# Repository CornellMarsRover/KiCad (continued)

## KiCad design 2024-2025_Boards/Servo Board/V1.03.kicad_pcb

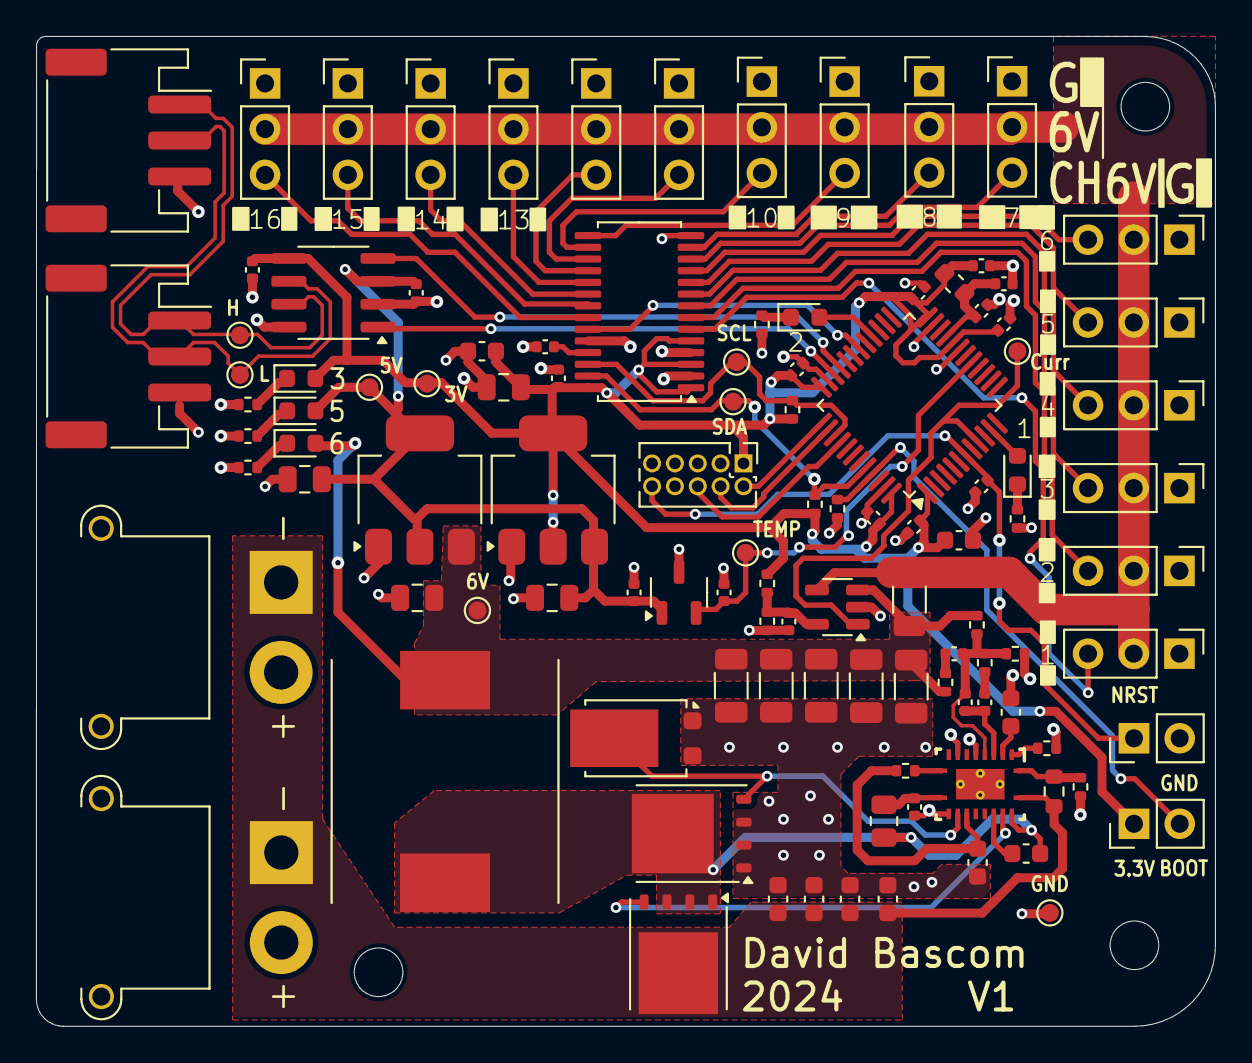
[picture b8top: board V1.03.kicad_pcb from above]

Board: 2 copper layers, 65.5 x 55.0 mm, 112 parts (0 on the bottom side), 58 nets.

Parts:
C1, C12: 10u; C_0603_1608Metric
C2, C3, C4, C5, C6, C10, C11, C13, C31: 100n; C_0402_1005Metric
C7: 10n; C_0402_1005Metric
C8, C9, C14, C15: 1u; C_0402_1005Metric
C16, C17: 0u1; C_0402_1005Metric
C27, C29: 10u; C_0805_2012Metric
C28, C30: 22u; C_0805_2012Metric
CBoot1: 0u1; C_0603_1608Metric
CC1: 2n2; C_0402_1005Metric
CC2: 47p; C_0402_1005Metric
CC3: 1.2n; C_0402_1005Metric
CIN1, CIN2, CIN3, CIN4: 4u7; C_0603_1608Metric
COUT1, COUT2, COUT3, COUT4, COUT5: 47; C_1206_3216Metric
CSS1: 47n; C_0603_1608Metric
CVcc1: 0u1; C_0603_1608Metric
Cilim1: 10p; C_0402_1005Metric
D1, D2, D3, D4, D5: GREEN; LED_0603_1608Metric
D6: SVT2060LB_R2_00001; TO-277B
FB1: 120R; L_0603_1608Metric
H1, H2, H3: MountingHole; MountingHole_2.7mm_M2.5
J1, J2: Conn_01x02_Pin; PinHeader_1x02_P2.54mm_Vertical
J3: Conn_ARM_JTAG_SWD_10; PinHeader_2x05_P1.27mm_Vertical
J4, J5: Conn_01x03_Socket; JST_PH_S3B-PH-SM4-TB_1x03-1MP_P2.00mm_Horizontal
J6, J7, J8, J9, J10, J11, J12, J13, J14, J15, J16, J17, J18, J19, J20, J21: Conn_01x03_Pin; PinHeader_1x03_P2.54mm_Vertical
J22, J23: Conn_01x02_Socket; AMASS_XT30PW-M_1x02_P2.50mm_Horizontal
L1: 2.7uH, 4.2mOhm; IND_AMDLA1306Q-101M
Q1, Q2: CSD18563Q5D; TDSON-8-1
R1, R9: 10k; R_0402_1005Metric
R2, R3: 4.7k; R_0402_1005Metric
R4: 1m; R_1206_3216Metric
R5: 100; R_0402_1005Metric
R6, R7, R16, R17: 1k; R_0402_1005Metric
R8: 2.2k; R_0402_1005Metric
RC1: 15k; R_0402_1005Metric
RC2: 3160; R_0402_1005Metric
RFB1: 20k; R_0402_1005Metric
RFB2: 3k09; R_0402_1005Metric
RPGOOD1: 20k; R_0402_1005Metric
RRT1: 20k; R_0402_1005Metric
RUV1: 20k; R_0603_1608Metric
RUV2: 3k57; R_0402_1005Metric
Rilim1: 487; R_0805_2012Metric
TP1, TP2, TP3, TP4, TP5, TP6, TP7, TP8, TP9, TP10: TestPoint; TestPoint_Pad_D1.0mm
U1: STM32G431CBT6; LQFP-48_7x7mm_P0.5mm
U2: PCA9685PW; TSSOP-28_4.4x9.7mm_P0.65mm
U3: TCAN1057AEV-Q1; SOIC-8_3.9x4.9mm_P1.27mm
U4: LM25145RGYR; RGY0020B
U5: AMS1117-3.3; SOT-223-3_TabPin2
U6: AMS1117-5.0; SOT-223-3_TabPin2
U7: INA180A4; SOT-23-5
U9: MCP9700T-E/TT; SOT-23-3

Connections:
+2.8V: C31.1, R8.2, R9.1, U7.5 (V+)
+3.3V: C1.1, C2.1, C3.1, C4.1, C5.1, C6.1, C9.1, C12.1, C13.1, C15.1, C30.1, D3.2 (A), FB1.2, J2.1, J3.1 (VTref), R2.1, R3.1, R8.1, TP9.1, U1.1 (VBAT), U1.20 (VREF+), U1.24 (VDD), U1.36 (VDD), U1.48 (VDD), U2.1 (A0), U2.3 (A2), U2.5 (A4), U2.28 (VDD), U3.5 (VIO), U5.2 (VO)
+3.3VA: C7.1, C8.1, FB1.1, U1.21 (VDDA)
+5V: C14.1, C16.1, C28.1, C29.1, D2.1 (K), D2.2 (A), R16.1, TP8.1, U3.3 (VCC), U5.3 (VI), U6.2 (VO), U9.1 (V_{DD})
+6V: C27.1, COUT1.1, COUT2.1, COUT3.1, COUT4.1, COUT5.1, D1.2 (A), J6.2, J7.2, J8.2, J9.2, J10.2, J11.2, J12.2, J13.2, J14.2, J15.2, J16.2, J17.2, J18.2, J19.2, J20.2, J21.2, L1.2, R4.1, R4.2, RC2.2, RFB1.2, TP7.1, U6.3 (VI), U7.3 (+), U7.4 (-)
+P_BATT: CIN1.1, CIN2.1, CIN3.1, CIN4.1, J22.1, J23.1, Q1.5 (D), RUV1.1, U4.20 (VIN)
/MCU/BOOT0: J2.2, R1.1, U1.45 (PB8)
/MCU/Debug_LED1: D4.2 (A), U1.11 (PA3)
/MCU/Debug_LED2: D5.2 (A), U1.28 (PB14)
/MCU/SWCLK: J3.4 (SWCLK/TCK), U1.38 (PA14)
/MCU/SWDIO: J3.2 (SWDIO/TMS), U1.37 (PA13)
/PWM Chip/EXTCLK: C11.1, U2.25 (EXTCLK)
/Power/BST: CBoot1.1, U4.17 (BST)
/Power/EN: RUV1.2, RUV2.1, U4.1 (EN_UVLO)
/Power/FB_: CC2.2, CC3.1, RC1.2, RFB1.1, RFB2.2, U4.5 (FB)
/Power/HO: Q1.4 (G), U4.18 (HO)
/Power/ILIM: Cilim1.1, Rilim1.1, U4.11 (ILIM)
/Power/LO: D6.3 (K), Q2.4 (G), U4.13 (LO)
/Power/PGOOD: RPGOOD1.2, U4.10 (PGOOD)
/Power/SS_TRK: CSS1.2, U4.3 (SS_TRK)
/Power/SW_: CBoot1.2, L1.1, Q1.1 (S), Q1.2 (S), Q1.3 (S), Q2.5 (D), Rilim1.2, U4.19 (SW)
/Power/comp: CC1.1, CC2.1, U4.4 (COMP)
/Power/rt: RRT1.2, U4.2 (RT)
CAN+: J4.1, J5.1, TP2.1, U3.7 (CANH)
CAN-: J4.2, J5.2, TP1.1, U3.6 (CANL)
CH0: J6.3, U2.6 (LED0)
CH1: J7.3, U2.7 (LED1)
CH2: J8.3, U2.8 (LED2)
CH3: J9.3, U2.9 (LED3)
CH4: J10.3, U2.10 (LED4)
CH5: J11.3, U2.11 (LED5)
CH6: J12.3, U2.12 (LED6)
CH7: J13.3, U2.13 (LED7)
CH8: J14.3, U2.15 (LED8)
CH9: J15.3, U2.16 (LED9)
CH10: J16.3, U2.17 (LED10)
CH11: J17.3, U2.18 (LED11)
CH12: J18.3, U2.19 (LED12)
CH13: J19.3, U2.20 (LED13)
CH14: J20.3, U2.21 (LED14)
CH15: J21.3, U2.22 (LED15)
CSA_OUT: TP5.1, U1.9 (PA1), U7.1
FDCAN_RX: U1.33 (PA11), U3.4 (RXD)
FDCAN_TX: U1.34 (PA12), U3.1 (TXD)
GND: C1.2, C2.2, C3.2, C4.2, C5.2, C6.2, C7.2, C8.2, C9.2, C10.2, C11.2, C12.2, C13.2, C14.2, C15.2, C16.2, C17.2, C27.2, C28.2, C29.2, C30.2, C31.2, CIN1.2, CIN2.2, CIN3.2, CIN4.2, COUT1.2, COUT2.2, COUT3.2, COUT4.2, COUT5.2, CSS1.1, CVcc1.2, Cilim1.2, D6.1 (A), D6.2 (A), J1.2, J3.3 (GND), J3.5 (GND), J3.9 (GNDDetect), J4.3, J5.3, J6.1, J7.1, J8.1, J9.1, J10.1, J11.1, J12.1, J13.1, J14.1, J15.1, J16.1, J17.1, J18.1, J19.1, J20.1, J21.1, J22.2, J23.2, Q2.1 (S), Q2.2 (S), Q2.3 (S), R1.2, R5.2, R6.2, R7.2, R9.2, R16.2, R17.2, RFB2.1, RRT1.1, RUV2.2, TP10.1, U1.19 (VSSA), U1.23 (VSS), U1.35 (VSS), U1.47 (VSS), U2.2 (A1), U2.4 (A3), U2.14 (VSS), U2.24 (A5), U3.2 (GND), U3.8 (STB), U4.6 (AGND), U4.8 (SYNCIN), U4.12 (PGND), U4.V, U5.1 (GND), U6.1 (GND), U7.2 (GND), U9.3 (GND)
NREST: C10.1, J1.1, J3.10 (~RESET), U1.7 (PG10)
unnamed: CC1.2, RC1.1
unnamed: CC3.2, RC2.1
unnamed: D1.1 (K), R5.1
unnamed: D3.1 (K), R17.1
unnamed: D4.1 (K), R6.1
unnamed: D5.1 (K), R7.1
unnamed: CVcc1.1, RPGOOD1.1, U4.14 (VCC)
PWM_OE: U1.30 (PA8), U2.23 (~OE)
PWM_SCL: R3.2, TP3.1, U1.39 (PA15), U2.26 (SCL)
PWM_SDA: R2.2, TP4.1, U1.44 (PB7), U2.27 (SDA)
SWO: J3.6 (SWO/TDO), U1.40 (PB3)
TEMP: C17.1, TP6.1, U1.17 (PB1), U9.2 (V_{OUT})

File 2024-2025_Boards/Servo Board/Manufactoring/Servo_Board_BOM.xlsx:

|  |  | Bill of Materials, Servo Board V1.03
Item # | *Designator | *Qty | Manufacturer | *Mfg Part # | Description / Value | *Package/Footprint | Type | Your Instructions / Notes
1 | C1, C12 | 2 | Samsung Electro-Mechanics | CL10A106MQ8NNNC | 10uF | 0603 | SMD
2 | C2, C3, C4, C5, C6, C10, C11, C13, C31 | 9 | Samsung Electro-Mechanics | CL05B104KP5NNNC | 100nF | 0402 | SMD
3 | C7 | 1 | Samsung Electro-Mechanics | CL05B103KB5NNNC | 10nF | 0402 | SMD
4 | C8, C9, C14, C15 | 4 | Samsung Electro-Mechanics | CL05A105KP5NNNC | 1uF | 0402 | SMD
5 | C16, C17 | 2 | Samsung Electro-Mechanics | CL05B104KP5NNNC | 0.1uF | 0402 | SMD
6 | C27, C29 | 2 | Samsung Electro-Mechanics | CL21A106KOQNNNE | 10uF | 0805 | SMD
7 | C28, C30 | 2 | Samsung Electro-Mechanics | CL21A226MQQNNNE | 22uF | 0805 | SMD
8 | CBoot1, CVcc1 | 2 | Samsung Electro-Mechanics | CL10B104KB8NNNC | 0.1uF | 0603 | SMD
9 | CC1 | 1 | Samsung Electro-Mechanics | CL05B222KB5VPNC | 2.2nF | 0402 | SMD
10 | CC2 | 1 | Samsung Electro-Mechanics | CL05C470JB5NNNC | 47pF | 0402 | SMD
11 | CC3 | 1 | YAGEO | CC0402KRX7R9BB122 | 1.2nF | 0402 | SMD
12 | Cilim1 | 1 | Samsung Electro-Mechanics | CL05C100JB5NNNC | 10pF | 0402 | SMD
13 | CIN1. CIN2, CIN3, CIN4 | 4 | Samsung Electro-Mechanics | CL10B475KQ8NQNC | 4.7uF | 0603 | SMD
14 | COUT1, COUT2, COUT3, COUT4, COUT5 | 5 | TDK Corporation | C3216JB1A476M160AB | 47uF | 1206 | SMD
15 | CSS1 | 1 | Samsung Electro-Mechanics | CL10B473KO8NNNC | 47nF | 0603 | SMD
16 | D1, D2, D3, D4, D5 | 5 | Würth Elektronik | 150060GS75000 | GREEN | 0603 | SMD
17 | D6 | 1 | Panjit International Inc. | SVT2060LB_R2_00001 | Schottky Diode 60 V 20A | TO-277B | SMD
18 | FB1 | 1 | Murata Electronics | BLM18KG121TN1D | 120 Ohms @ 100MHz Ferrite Bead | 0603 | SMD
19 | J1, J2 | 2 | Würth Elektronik | 61300211121 | 1x2 2.54mm Vertical Pin Header | 1x2_P2.54mm | THT
20 | J3 | 1 | GCT | BD120-10-A-0305-0229-L-B | 2x5 1.27mm Vertical Pin Header | 2x5_P1.27mm | THT
21 | J4, J5 | 2 | JST Sales America Inc. | S3B-PH-SM4-TB | JST 3 Pin Connector | JST_PH_S3B-PH-SM4-TB_1x03-1MP_P2.00mm_Horizontal | SMD
22 | J6 - J21 | 16 | Würth Elektronik | 61300311121 | 1x3 2.54mm Vertical Pin Header | 1x3_P2.54mm | THT
23 | J22, J23 | 2 | AMASS | XT30PW-M | XT30 Connector | AMASS_XT30PW-M_1x02_P2.50mm_Horizontal | THT
24 | L1 | 1 | Abracon LLC | AMDLA1306Q-2R7MT | 2.7uH, 4.2mOhm Inductor | Non-standard | SMD
25 | Q1, Q2 | 2 | Texas Instruments | CSD18563Q5A |  | TDSON-8-1 | SMD
26 | R1, R9 | 2 | Samsung Electro-Mechanics | RC1005F103CS | 10k | 0402 | SMD
27 | R2, R3 | 2 | YAGEO | RC0402FR-074K7L | 4.7k | 0402 | SMD
28 | R4 | 1 | YAGEO | PA1206FRE070R001Z | 1m | 1206 | SMD
29 | R5, R6, R7, R16, R17 | 5 | YAGEO | RC0402FR-071KL | 1k | 0402 | SMD
30 | R8 | 1 | YAGEO | RC0402FR-072K2L | 2.2k | 0402 | SMD
31 | RC1 | 1 | YAGEO | RC0402FR-0715KL | 15k | 0402 | SMD
32 | RC2 | 1 | YAGEO | RC0402FR-073K16L | 3160 Ohm | 0402 | SMD
33 | RFB1, RPGOOD1, RRT1 | 3 | YAGEO | RC0402FR-0720KL | 20k | 0402 | SMD
34 | RFB2 | 1 | YAGEO | RC0402FR-073K09L | 3.09k | 0402 | SMD
35 | Rilim1 | 1 | YAGEO | RC0805FR-07487RL | 487 Ohm | 0805 | SMD
36 | RUV1 | 1 | YAGEO | RC0603FR-0720KL | 20k | 0603 | SMD
37 | RUV2 | 1 | YAGEO | AC0402FR-073K57L | 3.57k | 0402 | SMD
38 | U1 | 1 | STMicroelectronics | STM32G431CBT6 | Microcontroller | LQFP-48_7x7mm_P0.5mm | SMD
39 | U2 | 1 | NXP USA Inc. | PCA9685PW,112 | PWM Signal Generator | TSSOP-28_4.4x9.7mm_P0.65mm | SMD
40 | U3 | 1 | Texas Instruments | TCAN1057AEVDRQ1 | FDCAN Transiever | SOIC-8_3.9x4.9mm_P1.27mm | SMD
41 | U4 | 1 | Texas Instruments | LM25145RGYR | Buck Converter | Non-standard | SMD
42 | U5 | 1 | EVVO | AMS1117-5.0 | 5V Regulator | SOT-223-3_TabPin2 | SMD
43 | U6 | 1 | UMW | AMS1117-3.3 | 3.3V Regulator | SOT-223-3_TabPin3 | SMD
44 | U7 | 1 | Texas Instruments | INA180A4IDBVR | Current Sensor | SOT-23-5 | SMD
45 | U9 | 1 | Microchip Technology | MCP9700T-E/TT | Temp Sensor | SOT-23-3 | SMD

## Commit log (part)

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2025-02-23 Schematic Finished
2025-02-25 Replaced footprints and new power/can connector
2025-03-04 New connector and board layout progress
2025-03-22 PCB Connected
2025-03-22 schematic reorganization
2025-03-23 Pins on correct side
2025-03-25 PCB Finished
2025-03-26 LED Board Finished
2025-03-29 Board fixes
2025-04-08 BDC Board
2025-04-08 fixes
2025-04-08 Add files via upload
    AUX kicad schematic added
2025-04-08 aux now au
2025-04-10 added servo and spectrometer board
2025-04-10 added poe board
2025-09-21 FDCAN-USB Board Initial Commit
2025-09-21 Symbol library fix
2025-09-21 Setup
2025-09-22 add backups
2025-09-24 Working on onboarding project
2025-09-24 Worked on onboarding project
2025-09-28 Finished KiCAD Schematic. Will start PCB Layout tomorrow.
2025-09-28 added onboarding board
2025-09-28 onboarding
2025-09-28 PCB Layout.
2025-09-29 Schematic done
2025-09-29 schematic files
2025-09-29 microcontroller pin update
2025-09-30 grouped components
2025-10-05 finalized schematic
2025-10-05 Layout work
2025-10-05 Worked on wiring.
2025-10-06 Finished arranging components
2025-10-10 almost finished wiring. gonna hook up grounds later
2025-10-11 completed(-ish) onboarding project
2025-10-13 Reorganized onboarding folder structure
2025-10-13 Finalized Onboarding (zone issues)
2025-10-15 new folders
2025-10-18 added buck converter
2025-10-18 minor edits
2025-10-26 added voltage regulators. wired lcd pinout. added fan pinouts. added 2nd buck converter.
2025-10-26 3.3->2.2V
2025-10-29 connected LCD pins to GPIO. Replicated ECORE fans and connectd to GPIO
2025-10-31 Layout finished
2025-11-09 Gerber files, BOM, layout fix
2025-11-09 Fixed fan pins in schematic. Started PCB layout. Wiring LDOs and buck converters.
2025-11-10 Final Design Reupload
2025-11-12 Worked on PCB. Have to change some track widths.
2025-11-13 USB swap and updated BOM
2025-11-14 Fan connectors broken+buggy. Fixed it. Accidentally deleted ground plane. Will have to add back. To get done by start of work session on Sunday: Hook up all fan connectors. Hook up temperature sensor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
2025-11-15 Kept wiring. To-do tomorrow: add back ground plane. Hook up ground vias. Wire LCD. Potentially reorganize the fan connectors. Wire fans together.
2025-11-16 Almost finished wiring. Just need to adjust widths and check configuration before finalizing design
2025-11-16 Adjusted widths for voltage safety.
2025-11-16 Finishing up
2025-11-16 minor updates
2025-11-17 finishing the board. debuggign,ectc
2025-11-19 Current servo board
2025-11-19 Added test LEDs
2025-12-02 tweak
2025-12-02 gerber zip
2025-12-14 finalizing board
2025-12-14 Finalizations
2025-12-14 remove KiCad lock file
2025-12-14 Fix onboarding locations
2025-12-14 finalizing
2025-12-19 Finalized board
2025-12-19 fixed can
2025-12-20 Started layout
2025-12-20 fixed differential pair and made new lcd wiring
2025-12-20 continued layout
2025-12-22 redid led display. can i delete the 2.2v regulator?
2025-12-23 redid led display.
2025-12-25 finished fan board
2025-12-25 fan board updates
2025-12-25 wtf is this doing here
2025-12-25 rehashed
2025-12-26 reduced #vias
2025-12-26 added power
2025-12-26 update stepper files locations
2025-12-26 moved 5v regulator closer
2025-12-27 moved 3.3v decoup cap somewhere else
2025-12-30 added parts
2025-12-30 found driver
2025-12-30 add driver
2025-12-31 finished driver
2025-12-31 saves
2025-12-31 added general parts
2025-12-31 help
2026-01-01 add logo
2026-01-02 add all pins to mcu and TCAN
2026-01-02 added labels
2026-01-05 add stuff
2026-01-05 Rename AU.kicad_sch to AUX.kicad_sch
2026-01-05 fix problems
2026-01-05 Rename AUX.kicad_sch to AUX_Port.kicad_sch
2026-01-05 auxport no longer name problem
2026-01-30 finished pcb hopefully forever
2026-03-15 changed fan board production files
